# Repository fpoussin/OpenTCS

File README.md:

OpenTCS
=======

Open source traction control and strain gauge quickshifter for race bikes.

### board
**1591XXA.pdf** Plans for the case  
**F0.ioc** used with ST's MicroXplorer app.  
**board.brd** Eagle 6 board file.  
**board.sch** Eagle 6 schematic file.  
**shifter.asc** LTSpice simulation for the ignition cut.  

### code
**inc**	include files  
**lib**	STM32F0 Peripheral library  
**os**  ChibiOS/Nil RTOS  
**src**	source files  

### gui
**inc**	include files  
**lib**	external libraries  
**src**	source files  
**ui**  QT designer files

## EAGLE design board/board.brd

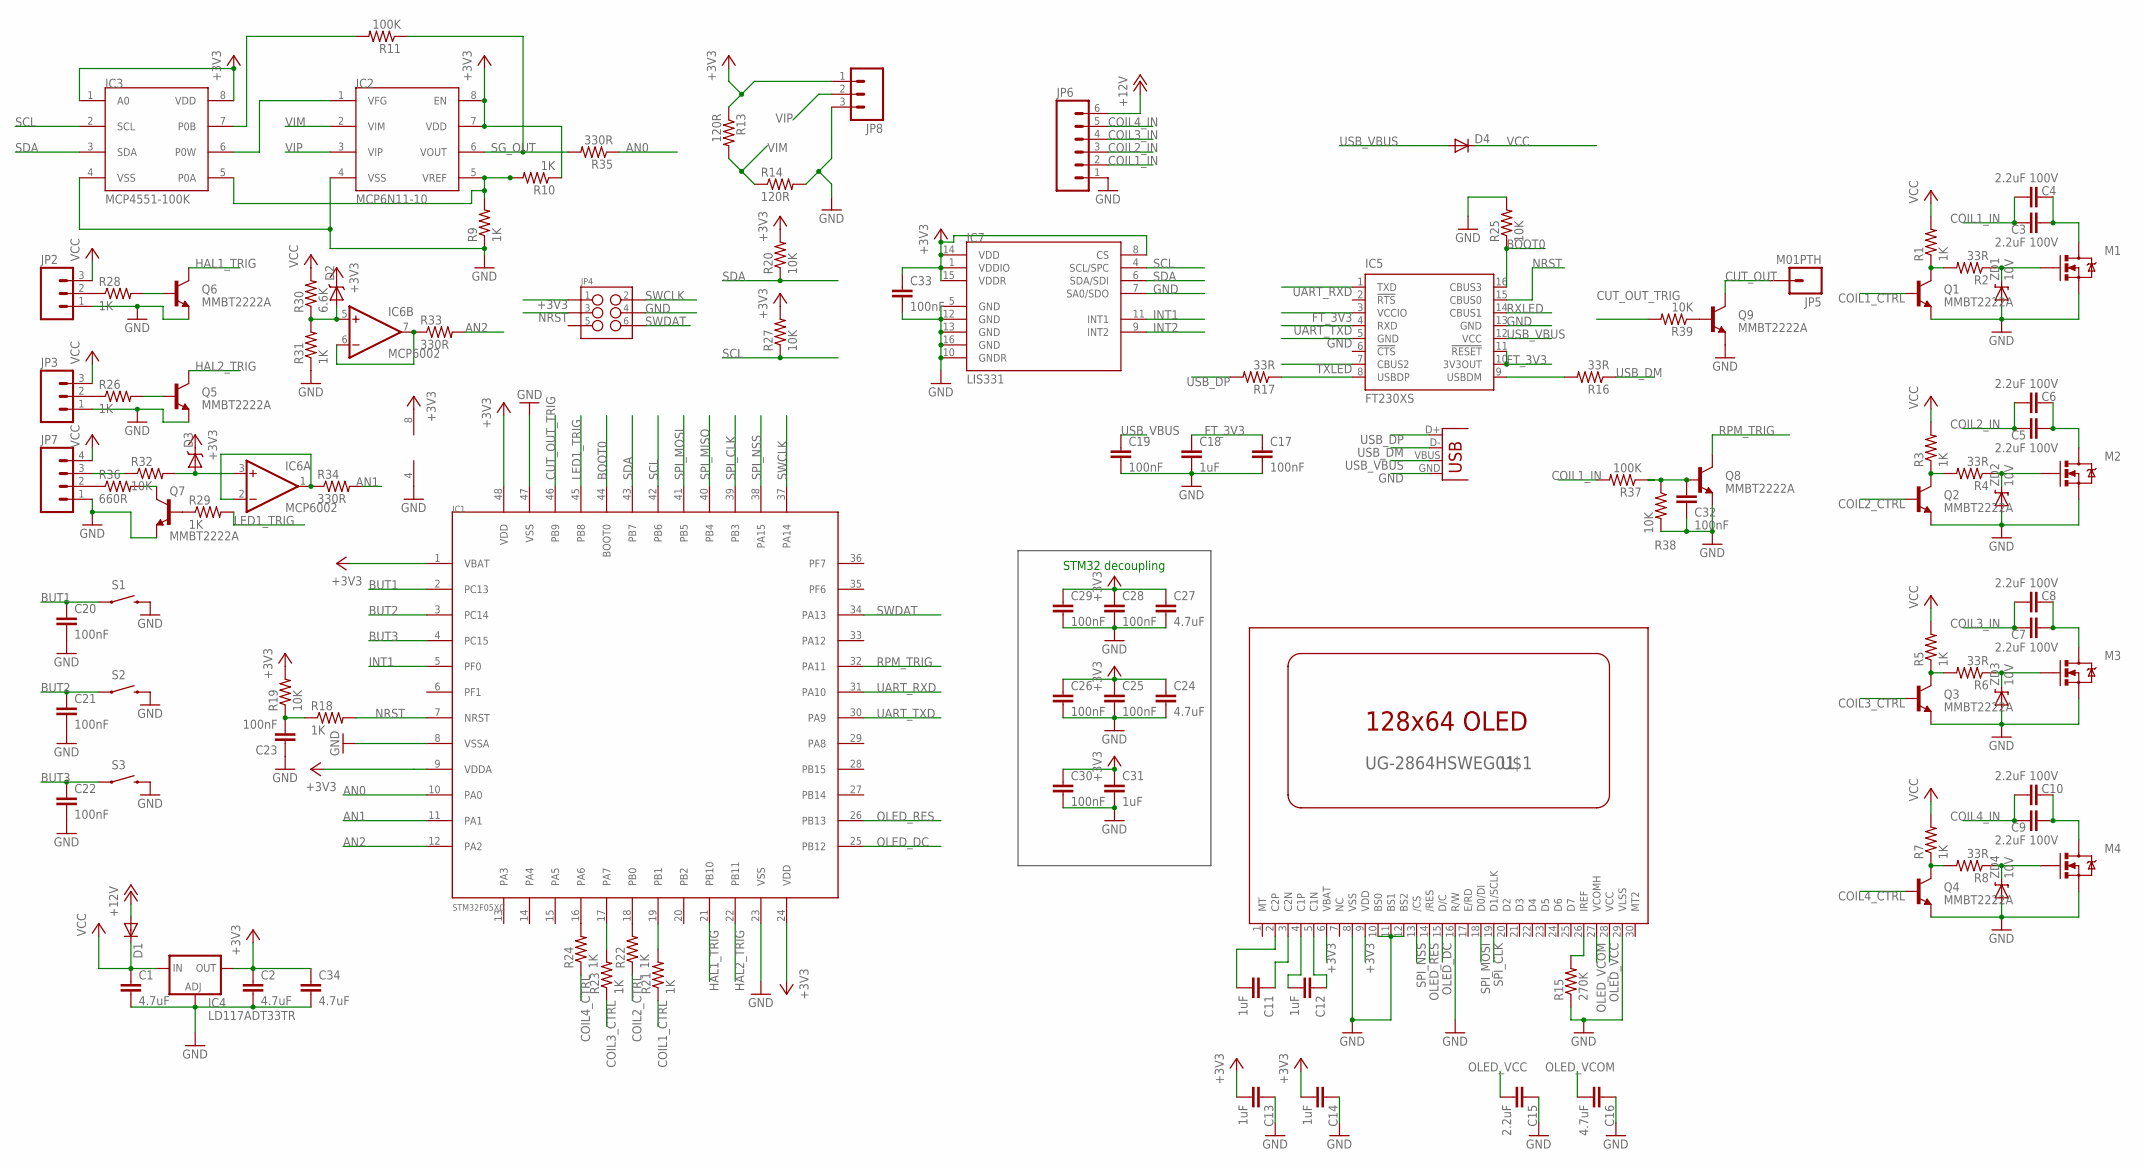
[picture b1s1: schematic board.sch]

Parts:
C1, C2, C16, C24, C27, C34: 4.7uF; 0603-CAP
C3, C4, C5, C6, C7, C8, C9, C10: 2.2uF 100V; 1206
C11, C12, C13, C14, C18, C31: 1uF; 0603-CAP
C15: 2.2uF; 0603-CAP
C17, C19, C20, C21, C22, C23, C25, C26, C28, C29, C30, C32, C33: 100nF; 0603-CAP
D1, D4: DIODESMA; SMA-DIODE
D2, D3: BAT20JFILM; SOD-323
IC1: STM32F05XC; LQFP-48
IC2: MCP6N11-10; SO08
IC3: MCP4551-100K; MSOP-8
IC4: LD117ADT33TR; DPACK
IC5: FT230XS; SSOP16
IC6: MCP6002; SO08
IC7: LIS331; LGA16-3MM
JP1: USBSMD; USB-MINIB
JP2, JP3, JP8: M03PTH; 1X03
JP4: M03X22X3_SILK_SM; 2X3
JP5: M01PTH; 1X01
JP6: M063.5MM-6; SCREWTERMINAL-3.5MM-6
JP7: M04PTH; 1X04
M1, M2, M3, M4: MOSFET-NCHANNELFDD8580; DPAK
Q1, Q2, Q3, Q4, Q5, Q6, Q7, Q8, Q9: MMBT2222A; SOT23
R1, R3, R5, R7, R9, R10, R18, R21, R22, R23, R24, R26, R28, R29, R31: 1K; 0603-RES
R2, R4, R6, R8, R16, R17: 33R; 0603-RES
R11: 100K; 0603-RES
R13, R14: 120R; 0603-RES
R15: 270K; 0603-RES
R19, R20, R25, R27, R32, R38, R39: 10K; 0603-RES
R30: 6.6K; 0603-RES
R33, R34, R35: 330R; 0603-RES
R36: 660R; 1206
R37: 100K; 1206
S1, S2, S3: SWITCH-MOMENTARY-2; TACTILE_SWITCH_TALL
U$1: UG-2864HSWEG01; 1X30-0.7MM
ZD1, ZD2, ZD3, ZD4: 10V; SOD-323

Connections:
+3V3: C2.1, C13.2, C14.2, C24.1, C25.1, C26.1, C27.1, C28.1, C29.1, C30.1, C31.1, C33.1, C34.1, D2.1 (C), D3.1 (C), IC1.1 (VBAT), IC1.9 (VDDA), IC1.24 (VDD), IC1.48 (VDD), IC2.7 (VDD), IC2.8 (EN), IC3.1 (A0), IC3.8 (VDD), IC4.4 (OUT), IC6.8 (V+), IC7.1 (VDDIO), IC7.8 (CS), IC7.14 (VDD), IC7.15 (VDDR), JP4.1, JP8.1, R10.1, R13.1, R19.2, R20.2, R27.2, U$1.6 (VBAT), U$1.9 (VDD)
+12V: D1.A, JP6.6
AN0: IC1.10 (PA0), R35.1
AN1: IC1.11 (PA1), R34.2
AN2: IC1.12 (PA2), R33.2
BOOT0: IC1.44 (BOOT0), IC5.16 (CBUS3), R25.1
BUT1: C20.1, IC1.2 (PC13), S1.A2 (1)
BUT2: C21.1, IC1.3 (PC14), S2.A2 (1)
BUT3: C22.1, IC1.4 (PC15), S3.A2 (1)
COIL1_CTRL: Q1.1 (B), R21.1
COIL1_IN: C3.1, C4.1, JP6.2, R37.2
COIL2_CTRL: Q2.1 (B), R22.1
COIL2_IN: C5.1, C6.1, JP6.3
COIL3_CTRL: Q3.1 (B), R23.1
COIL3_IN: C7.1, C8.1, JP6.4
COIL4_CTRL: Q4.1 (B), R24.1
COIL4_IN: C9.1, C10.1, JP6.5
CUT_OUT: JP5.1, Q9.3 (C)
CUT_OUT_TRIG: IC1.46 (PB9), R39.2
FT_3V3: C17.1, C18.1, IC5.3 (VCCIO), IC5.10 (3V3OUT), IC5.11 (!RESET)
GND: C1.2, C2.2, C13.1, C14.1, C15.1, C16.1, C17.2, C18.2, C19.2, C20.2, C21.2, C22.2, C23.1, C24.2, C25.2, C26.2, C27.2, C28.2, C29.2, C30.2, C31.2, C32.2, C33.2, C34.2, IC1.8 (VSSA), IC1.23 (VSS), IC1.47 (VSS), IC2.4 (VSS), IC3.4 (VSS), IC4.1 (ADJ), IC5.5 (GND), IC5.13 (GND), IC6.4 (V-), IC7.5 (GND), IC7.7 (SA0/SDO), IC7.10 (GNDR), IC7.12 (GND), IC7.13 (GND), IC7.16 (GND), JP1.GND, JP2.1, JP3.1, JP4.4, JP6.1, JP7.1, JP8.3, M1.3 (S), M2.3 (S), M3.3 (S), M4.3 (S), Q1.2 (E), Q2.2 (E), Q3.2 (E), Q4.2 (E), Q5.2 (E), Q6.2 (E), Q7.2 (E), Q8.2 (E), Q9.2 (E), R9.1, R14.2, R15.1, R25.2, R31.1, R38.2, S1.B2 (2), S2.B2 (2), S3.B2 (2), U$1.8 (VSS), U$1.10 (BS0), U$1.11 (BS1), U$1.12 (BS2), U$1.16 (R/W), U$1.29 (VLSS), ZD1.2 (A), ZD2.2 (A), ZD3.2 (A), ZD4.2 (A)
HAL1_TRIG: IC1.21 (PB10), Q6.3 (C)
HAL2_TRIG: IC1.22 (PB11), Q5.3 (C)
INT1: IC1.5 (PF0), IC7.11 (INT1)
INT2: IC7.9 (INT2)
LED1_TRIG: IC1.45 (PB8), R29.2
unnamed: C3.2, C4.2, M1.4 (D)
unnamed: M1.1 (G), R2.1, ZD1.1 (C)
unnamed: C5.2, C6.2, M2.4 (D)
unnamed: M2.1 (G), R4.1, ZD2.1 (C)
unnamed: C7.2, C8.2, M3.4 (D)
unnamed: M3.1 (G), R6.1, ZD3.1 (C)
unnamed: C9.2, C10.2, M4.4 (D)
unnamed: M4.1 (G), R8.1, ZD4.1 (C)
unnamed: IC2.1 (VFG), IC3.6 (P0W)
unnamed: C12.2, U$1.4 (C1P)
unnamed: IC1.16 (PA6), R24.2
unnamed: IC2.5 (VREF), IC3.5 (P0A), R9.2, R10.2
unnamed: C12.1, U$1.5 (C1N)
unnamed: IC3.7 (P0B), R11.2
unnamed: C11.1, U$1.3 (C2N)
unnamed: C11.2, U$1.2 (C2P)
unnamed: C23.2, R18.1, R19.1
unnamed: R15.2, U$1.26 (IREF)
unnamed: IC1.17 (PA7), R23.2
unnamed: IC1.18 (PB0), R22.2
unnamed: IC5.8 (USBDP), R17.1
unnamed: IC5.9 (USBDM), R16.2
unnamed: IC1.19 (PB1), R21.2
unnamed: D2.2 (A), IC6.5 (+IN), R30.1, R31.2
unnamed: D3.2 (A), IC6.3 (+IN), R32.2
unnamed: JP7.3, R32.1
unnamed: Q7.1 (B), R29.1
unnamed: JP7.2, R36.1
unnamed: IC6.6 (-IN), IC6.7 (OUT), R33.1
unnamed: Q5.1 (B), R26.2
unnamed: JP3.2, R26.1
unnamed: Q6.1 (B), R28.2
unnamed: JP2.2, R28.1
unnamed: Q7.3 (C), R36.2
unnamed: IC6.1 (OUT), IC6.2 (-IN), R34.1
unnamed: C32.1, Q8.1 (B), R37.1, R38.1
unnamed: Q9.1 (B), R39.1
NMOS1_GATE: Q1.3 (C), R1.1, R2.2
NMOS2_GATE: Q2.3 (C), R3.1, R4.2
NMOS3_GATE: Q3.3 (C), R5.1, R6.2
NMOS4_GATE: Q4.3 (C), R7.1, R8.2
NRST: IC1.7 (NRST), IC5.15 (CBUS0), JP4.3, R18.2
OLED_DC: IC1.25 (PB12), U$1.15 (D/C)
OLED_RES: IC1.26 (PB13), U$1.14 (/RES)
OLED_VCC: C15.2, U$1.28 (VCC)
OLED_VCOM: C16.2, U$1.27 (VCOMH)
RPM_TRIG: IC1.32 (PA11), Q8.3 (C)
RXLED: IC5.14 (CBUS1)
SCL: IC1.42 (PB6), IC3.2 (SCL), IC7.4 (SCL/SPC), R27.1
SDA: IC1.43 (PB7), IC3.3 (SDA), IC7.6 (SDA/SDI), R20.1
SG_OUT: IC2.6 (VOUT), R11.1, R35.2
SPI_CLK: IC1.39 (PB3), U$1.19 (D1/SCLK)
SPI_MISO: IC1.40 (PB4)
SPI_MOSI: IC1.41 (PB5), U$1.18 (D0/DI)
SPI_NSS: IC1.38 (PA15), U$1.13 (/CS)
SWCLK: IC1.37 (PA14), JP4.2
SWDAT: IC1.34 (PA13), JP4.6
TXLED: IC5.7 (CBUS2)
UART_RXD: IC1.31 (PA10), IC5.1 (TXD)
UART_TXD: IC1.30 (PA9), IC5.4 (RXD)
USB_DM: JP1.D-, R16.1
USB_DP: JP1.D+, R17.2
USB_VBUS: C19.1, D4.A, IC5.12 (VCC), JP1.VBUS
VCC: C1.1, D1.C, D4.C, IC4.3 (IN), JP2.3, JP3.3, JP7.4, R1.2, R3.2, R5.2, R7.2, R30.2
VIM: IC2.2 (VIM), R13.2, R14.1
VIP: IC2.3 (VIP), JP8.2

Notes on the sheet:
STM32 decoupling

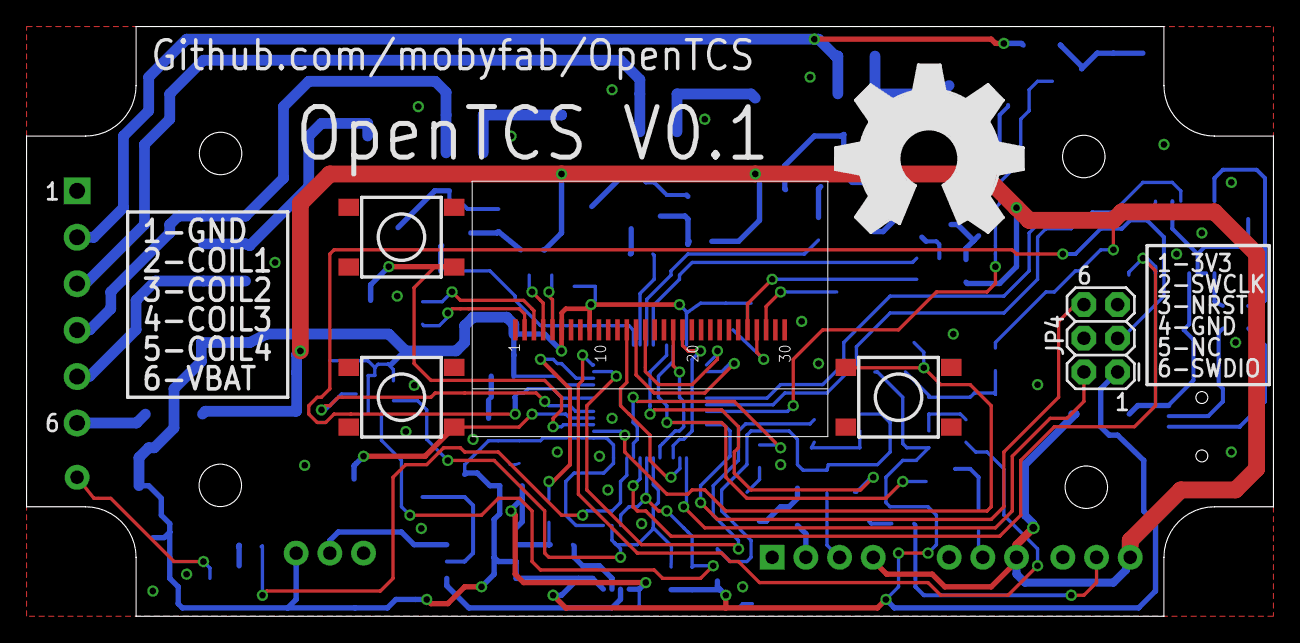
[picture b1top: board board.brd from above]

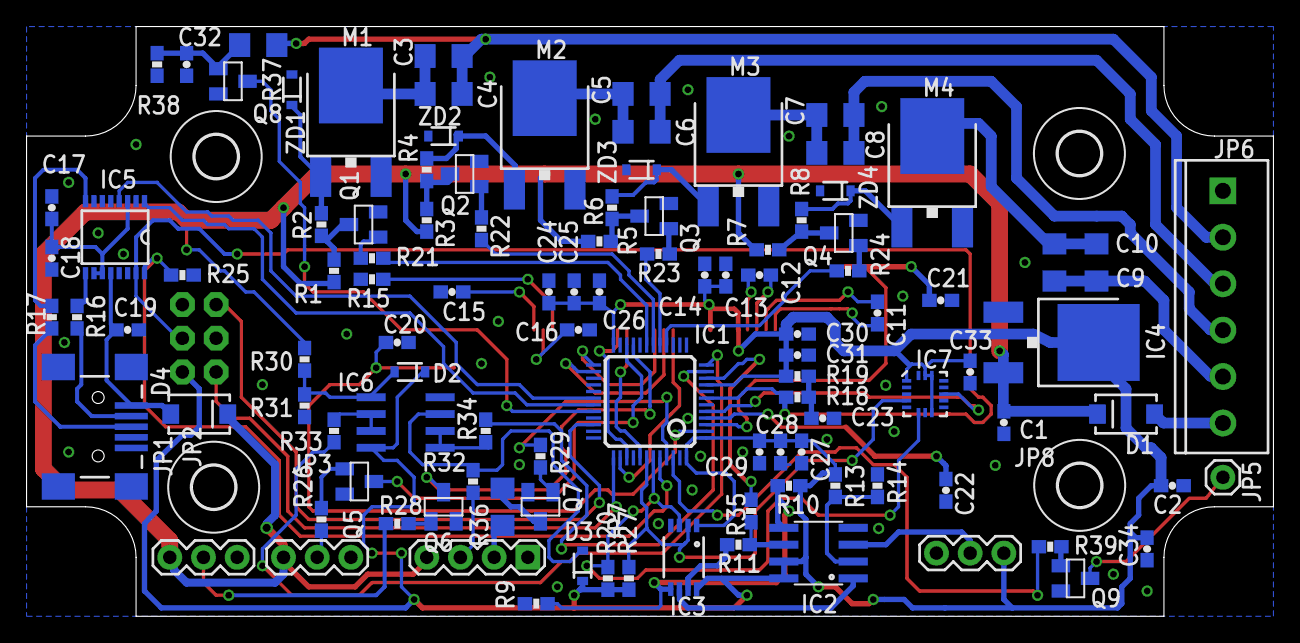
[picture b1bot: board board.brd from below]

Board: 2 copper layers, 94.0 x 44.5 mm, 117 parts (111 on the bottom side), 88 nets.

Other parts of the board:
U$2, U$3, U$4, U$5: 3,2
U$6: OSHW_FILLX500_NOTEXT

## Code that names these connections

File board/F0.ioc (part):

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Mcu.Name=STM32F050C(4-6)Tx
Mcu.Package=LQFP48
PA0.Mode=IN0
PA0.Signal=ADC_IN0
PA1.Mode=IN1
PA1.Signal=ADC_IN1
PA10.Mode=Asynchronous
PA10.Signal=USART1_RX
PA11.Signal=TIM1_CH4
PA13.Mode=Serial-WireDebug
PA13.Signal=SYS_SWDAT
PA14.Mode=Serial-WireDebug
PA14.Signal=SYS_SWCLK
PA15.Mode=Full-Duplex-Master_With-NSS
PA15.Signal=SPI1_NSS
PA2.Mode=IN2
PA2.Signal=ADC_IN2
PA6.Mode=Input-Capture
PA6.Signal=TIM3_CH1
PA7.Mode=Input-Capture
PA7.Signal=TIM3_CH2
PA9.Mode=Asynchronous
PA9.Signal=USART1_TX
PB0.Mode=Input-Capture
PB0.Signal=TIM3_CH3
PB1.Mode=Input-Capture
PB1.Signal=TIM3_CH4
PB10.Signal=TIM2_CH3
PB11.Signal=TIM2_CH4
PB12.Signal=GPIO_Output
PB13.Signal=GPIO_Output
PB3.Mode=Full-Duplex-Master_With-NSS
PB3.Signal=SPI1_SCK
PB4.Mode=Full-Duplex-Master_With-NSS
PB4.Signal=SPI1_MISO
PB5.Mode=Full-Duplex-Master_With-NSS
PB5.Signal=SPI1_MOSI
PB6.Mode=I2C
PB6.Signal=I2C1_SCL
PB7.Mode=I2C
PB7.Signal=I2C1_SDA
PB8.Mode=Input-Capture
PB8.Signal=TIM16_CH1
PC13.Signal=GPIO_Input
PC14-OSC32_IN.Signal=GPIO_Input
PC15-OSC32_OUT.Signal=GPIO_Input
PF0-OSC_IN.Signal=GPIO_Input

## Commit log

2013-08-21 Adding board files.
2013-08-21 Adding Nil RTOS, changed value of digital pot to proper part name.
2013-08-21 Moving code to proper folder.
2013-08-21 Adding peripheral library
2013-08-21 Updated makefile to link peripheral lib.
2013-08-21 Moving .h/.c files to proper inc/src folders.
2013-08-21 Removing unused files.
2013-08-21 Adding ignore file and QT creator project files.
2013-08-21 Adding mailboxes from chibios.
2013-08-22 Removed extra code.
2013-08-22 Adding some placeholders.
2013-08-22 Adding SSD1306 driver. (modified)
2013-08-22 Updated IO config.
2013-08-23 Adding some code for handling settings, ADC, etc.
2013-08-23 Adding M2TK library, will do some tests.
2013-08-23 Removed some useless files.
2013-08-23 Testing basic menu.
2013-08-23 Updated ignore file.
2013-08-23 Cleaning files.
2013-08-23 Work on menus.
2013-08-24 Updated display and menu code.
2013-08-24 Multiples code fixes.
2013-08-25 Updated code to use TIM14 for Nil's tickless mode.
2013-08-25 Updating code for tickless mode, added code for the light thread.
2013-08-26 Fixed systimer typedef to work with 16bit timers.
2013-08-26 Multiple updates. Mostly timers and DMA.
2013-08-26 Updated WWDG (watchdog) code.
2013-08-26 Work on the sensors thread. (I2C and Timers)
2013-08-26 Work on the sensors.
2013-08-26 Minor changes for sensors.
2013-08-26 Fixed a bunch of things
2013-08-27 Various changes, added semaphores and file for communication peripherals.
2013-08-27 Minor changes on semaphores.
2013-08-27 Adding code to freeze some timers while debugging. (SysTick and WWDG)
2013-08-27 Fixed wrong define. (WWDG)
2013-08-27 Timers / Interrupts changes.
2013-08-27 Changed semaphores signal.
2013-08-27 Updated SPI configuration and semaphores.
2013-08-27 Minor changes
2013-08-27 Fixed usart1 (DMA)
2013-08-28 Fixed ADC DMA code.
2013-09-01 Adding acceleration calculation.
2013-09-03 Updated makefiles and sensors.c
2013-09-09 Adding output for external fuel/igntion controller.
2013-09-10 Updated code related to timers (input capture)
2013-09-10 Minor updates: light and sensors threads
2013-09-10 Updated Timer code. Added more debugging for sensors.
2013-09-10 Minor fix.
2013-09-11 Moved WWDG reset detection code to WWDG thread.
2013-09-12 Updating sensor code.
2013-09-12 Updated cut time calculation. Added a new status structure.
2013-09-12 USART code update.
2013-09-13 UART code update
2013-09-17 Updated ADC sensors code.
2013-09-17 Updating to latest Chibios/Nil version.
2013-09-17 Removed useless include.
2013-09-17 minor update
2013-09-18 Updated timer code and project files list.
2013-09-18 Fixed missing IRQ vectors defines.
2013-09-18 Cleaning some includes and ISR code.
2013-09-18 Updated LIS331 I2C code.
2013-09-18 Updating ignition code with an ISR.
2013-09-18 Disabling LTO as it breaks the code.
2013-09-19 Updated ignition code.
2013-09-20 Updating ssd code.
2013-09-20 Updated Makefile.
2013-09-23 Adding gear management code.
2013-09-23 Menu code.
2013-09-23 Working on menus.
2013-09-24 Adding GUI base files.
2013-09-24 Adding some code for device handling and moving files.
2013-09-24 Typo.
2013-09-24 Minor fixes.
2013-09-25 Updated ftdi code with CBUS mux function.
2013-09-25 Adding stuff to UI.
2013-09-25 STM32 class to handle bootloader and reset.
2013-09-25 Minor changes.
2013-09-25 Minor fixes for cut time.
2013-09-25 Updated some of the serial protocol code.(for GUI)
2013-09-25 Adding some comments.
2013-09-25 Adding code to change settings via GUI.
2013-09-26 Moving stm and gui code to a proper "code" folder.
2013-09-26 Some cleaning.
2013-09-26 First implementation for Protocol Buffers.
2013-09-28 Removing QT creator user file.
2013-09-28 Updated GUI.
2013-09-28 updating data functions.
2013-09-29 Updated code around ftdi class.
2013-09-29 Updated GUI code for WIN32.
2013-09-30 Added some debug ouput.
2013-09-30 Fixed PB tag type size.
2013-09-30 Working on communication code and UI.
2013-10-09 Updating UI file.
2013-10-09 Another UI update.
2014-03-16 Changed connectors

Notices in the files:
parts and their libraries:
SparkFun-Passives: Licensing: CC v3.0 Share-Alike You are welcome to use this library for commercial purposes.
